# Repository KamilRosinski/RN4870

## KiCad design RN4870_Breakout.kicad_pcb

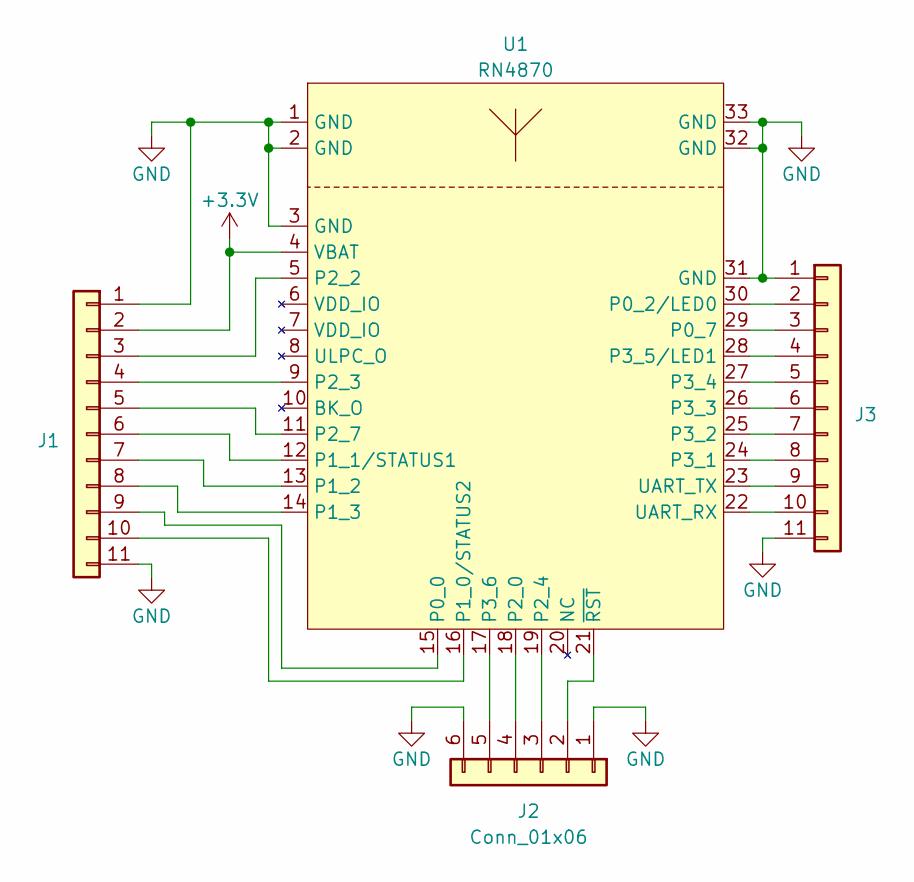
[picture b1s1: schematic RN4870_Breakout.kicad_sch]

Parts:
J1, J3: Conn_01x11; PinHeader_1x11_P2.54mm_Vertical
J2: Conn_01x06; PinHeader_1x06_P2.54mm_Vertical
U1: RN4870

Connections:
+3.3V: J1.2, U1.4 (VBAT)
GND: J1.1, J1.11, J2.1, J2.6, J3.1, J3.11, U1.1 (GND), U1.2 (GND), U1.3 (GND), U1.31 (GND), U1.32 (GND), U1.33 (GND)
unnamed: J1.3, U1.5 (P2_2)
unnamed: J1.4, U1.9 (P2_3)
unnamed: J1.5, U1.11 (P2_7)
unnamed: J1.6, U1.12 (P1_1/STATUS1)
unnamed: J1.7, U1.13 (P1_2)
unnamed: J1.8, U1.14 (P1_3)
unnamed: J1.9, U1.15 (P0_0)
unnamed: J1.10, U1.16 (P1_0/STATUS2)
unnamed: J2.2, U1.21 (~RST)
unnamed: J2.3, U1.19 (P2_4)
unnamed: J2.4, U1.18 (P2_0)
unnamed: J2.5, U1.17 (P3_6)
unnamed: J3.2, U1.30 (P0_2/LED0)
unnamed: J3.3, U1.29 (P0_7)
unnamed: J3.4, U1.28 (P3_5/LED1)
unnamed: J3.5, U1.27 (P3_4)
unnamed: J3.6, U1.26 (P3_3)
unnamed: J3.7, U1.25 (P3_2)
unnamed: J3.8, U1.24 (P3_1)
unnamed: J3.9, U1.23 (UART_TX)
unnamed: J3.10, U1.22 (UART_RX)

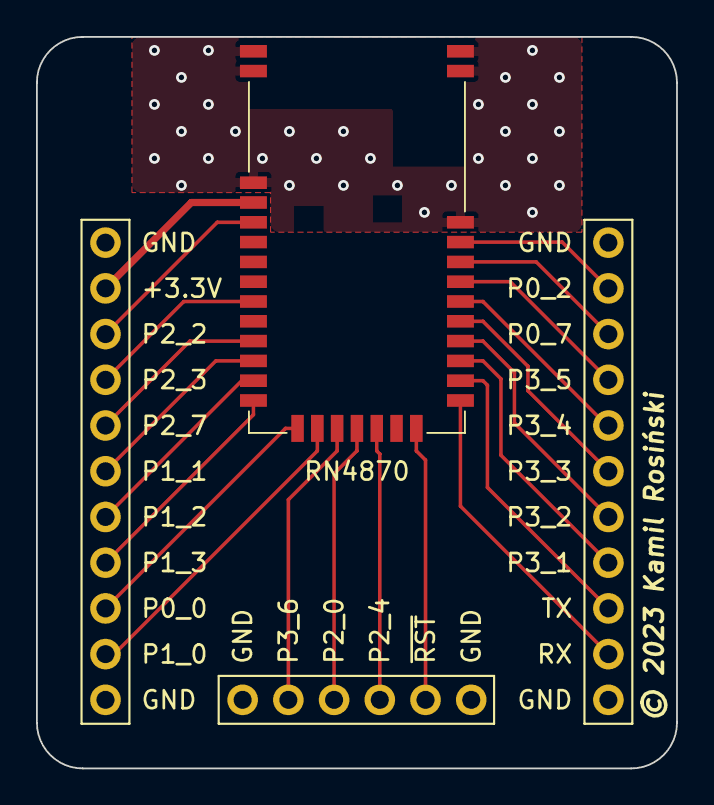
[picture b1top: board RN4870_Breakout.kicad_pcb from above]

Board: 2 copper layers, 35.6 x 40.6 mm, 4 parts (0 on the bottom side), 23 nets.

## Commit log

2023-04-16 Empty project
2023-04-16 Created RN4870 symbol
2023-04-16 Schematic
2023-04-17 Created RN4872 footprint
2023-04-17 .gitignore update
2023-04-17 Footprints assigned
2023-04-17 Moved origin point for RN4870 footprint
2023-04-20 RN4870 footprint: rotete thermal relief spokes
2023-04-20 RN4870 footprint: moved origin to edge of module
2023-04-21 PCB layout
2023-04-21 RN4870 footprint clean-up
2023-04-21 DRC fixes
2023-04-22 Post review fixes
2023-04-26 Gerbers generated

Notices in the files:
RN4870_Breakout.kicad_pcb:
© 2023 Kamil Rosiński
